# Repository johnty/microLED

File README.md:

#WS2812B LED mount for micro brushless motors

A simple breakout board that allows you to mount a WS2812B LED underneath a brushless motor (110x size). measured against Racerstar 1103 which has a 8.5mm diameter spacing between the screw holes. Space for a 805 SMD cap near the V+ and GNDof the LED package. 3-wire pin connectors for both DIN and DOUT for daisy chaining.

Using WS2812B library from https://github.com/madworm/WS2812B.pretty

version 0.1
31 August 2017
info@johnty.ca

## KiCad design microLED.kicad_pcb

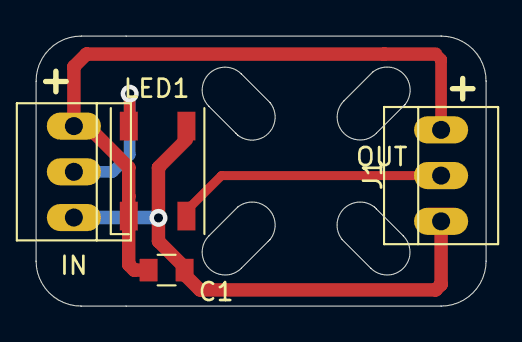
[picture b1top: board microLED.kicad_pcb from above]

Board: 2 copper layers, 25.0 x 15.0 mm, 4 parts (0 on the bottom side), 4 nets.

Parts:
C1: C1; C_0805
J1: OUT; PINHEAD1-3
J2: IN; PINHEAD1-3
LED1: WS2812B; LED_WS2812B-PLCC4

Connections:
unnamed: C1.1, J1.1, J2.3, LED1.1
unnamed: C1.2, J1.3, J2.1, LED1.3
unnamed: J1.2, LED1.4
unnamed: J2.2, LED1.2

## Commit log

2017-09-18 fixed gnd pad not connected on output side
